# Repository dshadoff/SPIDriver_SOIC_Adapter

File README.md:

# SPIDriver SOIC Adapter board

While most of my boards are basically electrical things with some mechanical aspects,
some of them are primarily mechnical things with some electrical aspects. This board
is one of those.

I have an ExCamera Labs SPIDriver ( https://www.crowdsupply.com/excamera/spidriver ), and
I've been using it to read/write to various types of SPI memory chips; the hookup wires
provided with the unit are certainly multipupose, but they aren't optimized for connection
the SPIDriver to the SOIC in-circuit chip clip.

Before:

After:

Assembly is simple:
1. First attach the two Harwin M20-7910642R header sockets on the SPIDriver's headers.
(Link to part: https://www.mouser.ca/ProductDetail/Harwin/M20-7910642R?qs=%2Fha2pyFaduh6CW27Bf4Ji3liOHxzgSHZx%252BrczPoIZ0OamkTSPd60Zw%3D%3D )

2. Position the PC board right up agains the SPIDriver board, and attach clips to hold
it in place while soldering takes place.

3. Add the 2-row headers and solder them in place.

I designed the board using the free version of EAGLE (2-layer, less than 100mm on both
X- and Y-axes).  The gerbers are included in this repository, in case you want to get your
own set made.

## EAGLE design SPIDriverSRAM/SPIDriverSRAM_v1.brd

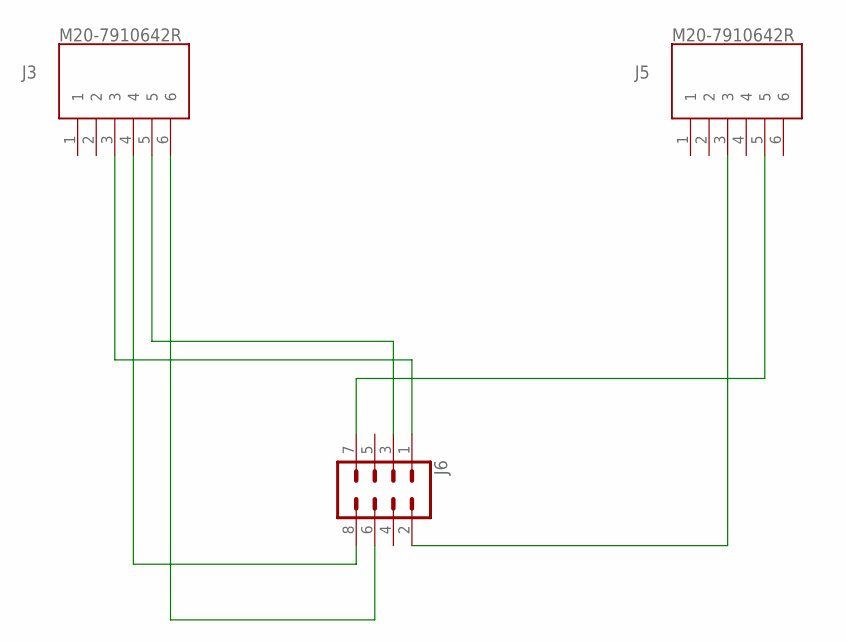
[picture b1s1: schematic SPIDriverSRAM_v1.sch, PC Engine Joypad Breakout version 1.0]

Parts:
J3, J5: M20-7910642R
J6: CONN_04X2; 2X4

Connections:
unnamed: J3.3, J6.1
unnamed: J3.5, J6.3
unnamed: J5.5, J6.7
unnamed: J5.3, J6.2
unnamed: J3.4, J6.8
unnamed: J3.6, J6.6

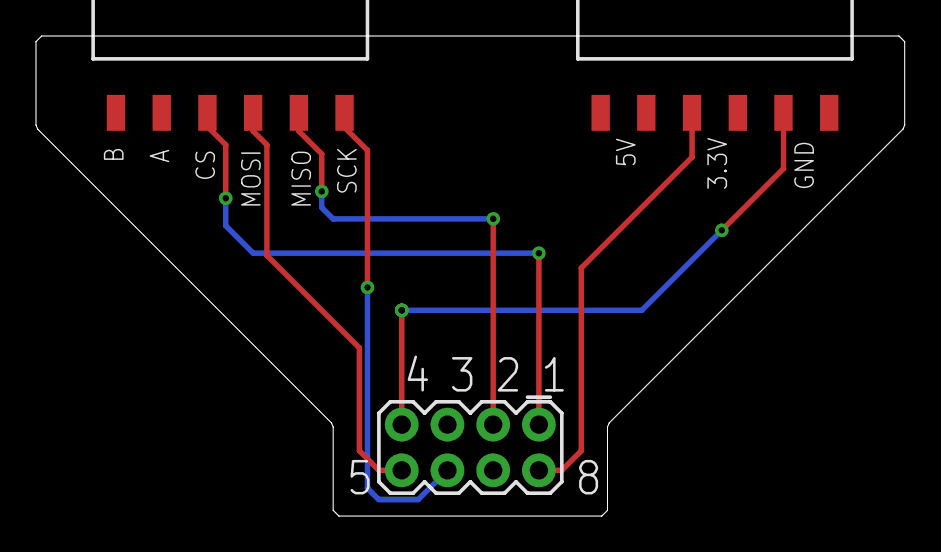
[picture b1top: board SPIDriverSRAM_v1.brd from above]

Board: 2 copper layers, 48.3 x 26.7 mm, 3 parts (0 on the bottom side), 6 nets.

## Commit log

2020-07-09 Update README & Pics

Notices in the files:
parts and their libraries:
SparkFun-Connectors: Licensing: Creative Commons ShareAlike 4.0 International - https://creativecommons.org/licenses/by-sa/4.0
